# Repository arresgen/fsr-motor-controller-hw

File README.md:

# Op-Amp & Comparator Controller Board

A KiCad hardware design project featuring an operational amplifier signal conditioning circuit and comparator-driven DC motor and LED indicator control.

---

## Technical Specifications & Features

* **Primary Supply Voltage:** +5V DC
* **Operational Amplifier:** Texas Instruments LM358 (Dual Low-Power Op-Amp)
* **Comparator:** Texas Instruments LM393 (Dual Low-Power Comparator)
* **Sensor Connector:** JST-EH 2-Pin header labeled for Force Sensitive Resistor (FSR402)
* **Actuator Output:** Transistor-driven (2N2222 NPN) DC Motor driver stage with flyback diode protection (1N4007)
* **Visual Indicator:** LED status circuit (D1) driven via comparator thresholding
* **Test Points:** Dedicated test points (`TP1` through `TP6`) for signal probing and hardware validation
* **Form Factor:** Compact 2-layer PCB (50.8 mm x 76.2 mm / KiCad 10.0 standard layer stack)[cite: 2]

---

## Circuit Overview

1. **Input Stage:** The input signal connects via connector `J1` (FSR402 sensor). Resistors `R1` (1.5k) and `R2` (10k) provide biasing and initial signal division.
2. **Amplification & Conditioning Stage (LM358):** Unit `U1` buffers and amplifies the analog input signal. Potentiometer `RV1` (10k) allows adjustable gain/reference tuning.
3. **Thresholding & Comparison Stage (LM393):** Dual comparator `U2` compares the processed signal against adjustable resistor network references (`R3` 100k, `R4` 6.8k).
4. **Output Driver Stage:**
   * **LED Drive:** Open-collector output drives status LED `D1` through limiting resistor `R6` (4.7k).
   * **Motor Drive:** Comparator output switches NPN transistor `Q2` (2N2222) via base resistor `R7` (100Ω) to power DC Motor `M1`. Free-wheeling diode `D2` (1N4007) suppresses inductive voltage spikes.

---

## Component List (BOM)

| Reference | Value / Part | Description | Footprint / Package |
| :--- | :--- | :--- | :--- |
| **U1** | LM358 | Low-Power Dual Op-Amp | DIP-8 Socket |
| **U2** | LM393 | Dual Voltage Comparator | DIP-8 Socket |
| **Q2** | 2N2222 | General Purpose NPN Transistor | TO-92L Inline Wide |
| **D1** | LED | Status Indicator | JST-EH 2-Pin / THT |
| **D2** | 1N4007 | 1000V 1A Rectifier Diode | DO-41 Horizontal |
| **M1** | Motor_DC | DC Motor Output | JST-EH 2-Pin Header |
| **J1** | FSR402 | Sensor Connector Input | JST-EH 2-Pin Vertical |
| **J2** | DC Source | +5V / GND Power Input | JST-EH 2-Pin Vertical |
| **RV1** | 10k | Potentiometer | JST-EH 3-Pin / Trim Pot |
| **R1** | 1.5k | Axial Resistor, 1/4W | DIN0207 (10.16mm Pitch) |
| **R2, R5** | 10k, 1k | Axial Resistors, 1/4W | DIN0207 (10.16mm Pitch) |
| **R3, R4** | 100k, 6.8k | Axial Resistors, 1/4W | DIN0207 (10.16mm Pitch) |
| **R6, R7** | 4.7k, 100 | Axial Resistors, 1/4W | DIN0207 (10.16mm Pitch) |
| **C1 - C5** | 100n / 22n | Ceramic Disc Decoupling Capacitors | Disc D5.0mm / P5.00mm |

---

## Test Point Reference

* **TP1:** Input signal node post-FSR biasing stage
* **TP2:** Non-inverting operational amplifier stage output/input node
* **TP3:** Voltage reference/bias node
* **TP4:** Comparator output signal node
* **TP5:** Secondary op-amp output stage
* **TP6:** Motor drive / low-side control node

---

## Project Structure

```text
.
├── fsr-motor-controller-hw.kicad_sch    # Schematic Source File
├── fsr-motor-controller-hw.kicad_pcb    # PCB Layout Source File
└── README.md                                  # Documentation

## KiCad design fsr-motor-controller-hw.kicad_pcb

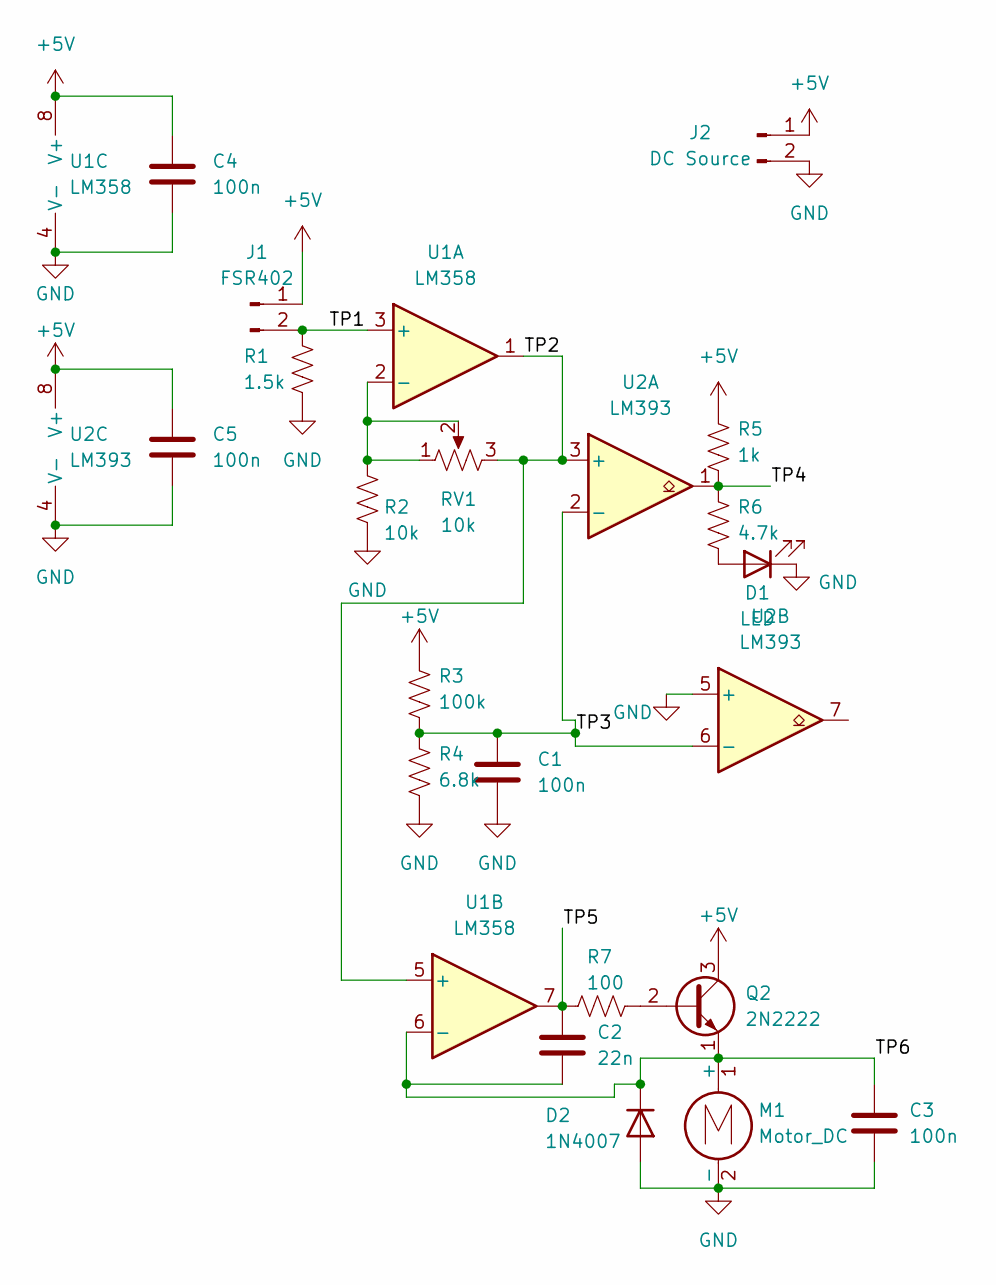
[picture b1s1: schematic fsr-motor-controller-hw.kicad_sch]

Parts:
C1, C3, C4, C5: 100n; C_Disc_D5.0mm_W2.5mm_P5.00mm
C2: 22n; C_Disc_D5.0mm_W2.5mm_P5.00mm
D1: LED; JST_EH_B2B-EH-A_1x02_P2.50mm_Vertical
D2: 1N4007; D_DO-41_SOD81_P10.16mm_Horizontal
J1: FSR402; JST_EH_B2B-EH-A_1x02_P2.50mm_Vertical
J2: DC Source; JST_EH_B2B-EH-A_1x02_P2.50mm_Vertical
M1: Motor_DC; JST_EH_B2B-EH-A_1x02_P2.50mm_Vertical
Q2: 2N2222; TO-92L_Inline_Wide
R1: 1.5k; R_Axial_DIN0207_L6.3mm_D2.5mm_P10.16mm_Horizontal
R2: 10k; R_Axial_DIN0207_L6.3mm_D2.5mm_P10.16mm_Horizontal
R3: 100k; R_Axial_DIN0207_L6.3mm_D2.5mm_P10.16mm_Horizontal
R4: 6.8k; R_Axial_DIN0207_L6.3mm_D2.5mm_P10.16mm_Horizontal
R5: 1k; R_Axial_DIN0207_L6.3mm_D2.5mm_P10.16mm_Horizontal
R6: 4.7k; R_Axial_DIN0207_L6.3mm_D2.5mm_P10.16mm_Horizontal
R7: 100; R_Axial_DIN0207_L6.3mm_D2.5mm_P10.16mm_Horizontal
RV1: 10k; JST_EH_B3B-EH-A_1x03_P2.50mm_Vertical
U1: LM358; DIP-8_W7.62mm_Socket_LongPads
U2: LM393; DIP-8_W7.62mm_Socket_LongPads

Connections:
+5V: C4.1, C5.1, J1.1, J2.1, Q2.3 (C), R3.1, R5.1, U1.8 (V+), U2.8 (V+)
/TP1: J1.2, R1.1, U1.3 (+)
/TP2: RV1.3, U1.1, U1.5 (+), U2.3 (+)
/TP3: C1.1, R3.2, R4.1, U2.2 (-), U2.6 (-)
/TP4: R5.2, R6.1, U2.1
/TP5: C2.1, R7.1, U1.7
/TP6: C2.2, C3.1, D2.1 (K), M1.1 (+), Q2.1 (E), U1.6 (-)
GND: C1.2, C3.2, C4.2, C5.2, D1.1 (K), D2.2 (A), J2.2, M1.2 (-), R1.2, R2.2, R4.2, U1.4 (V-), U2.4 (V-), U2.5 (+)
unnamed: D1.2 (A), R6.2
unnamed: Q2.2 (B), R7.2
unnamed: R2.1, RV1.1, RV1.2, U1.2 (-)

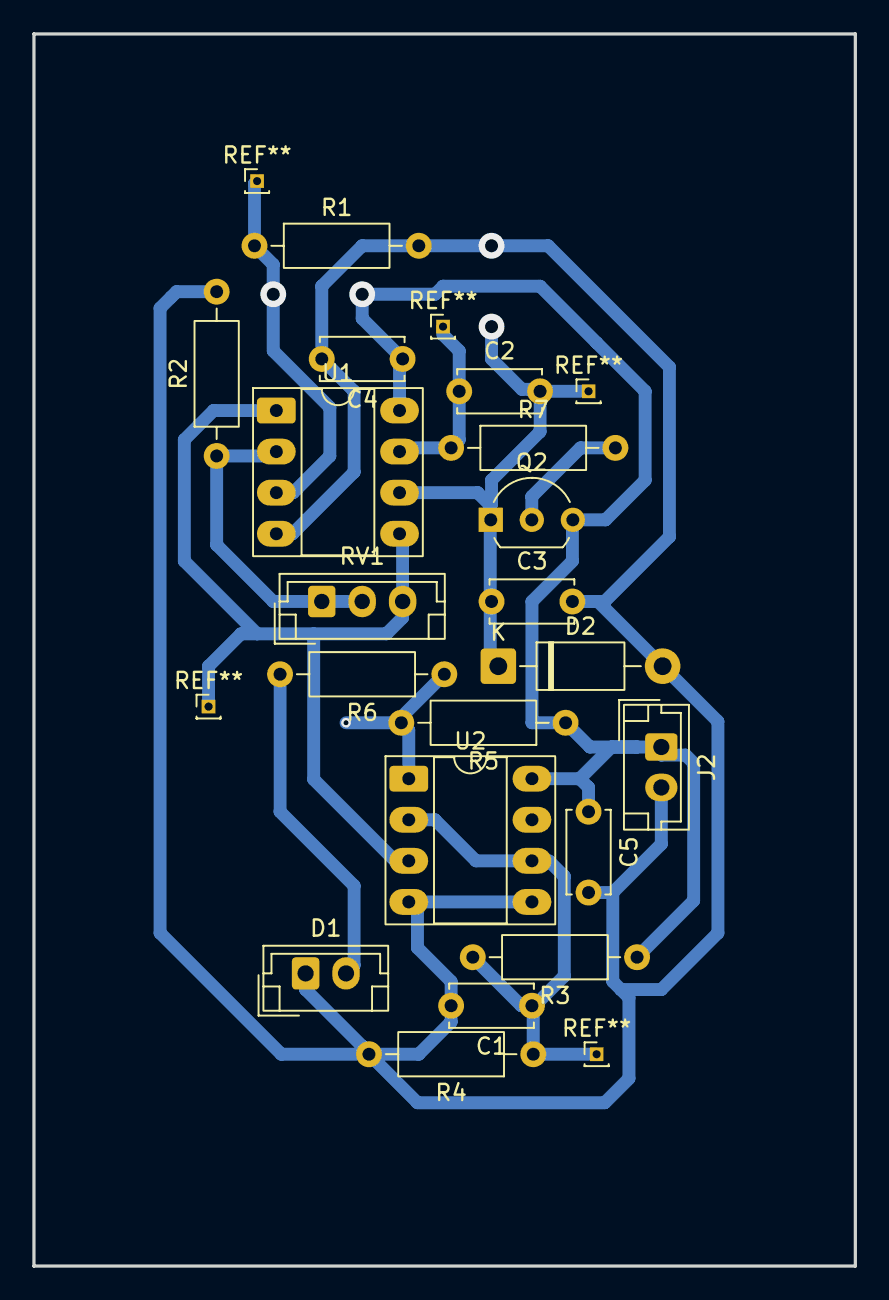
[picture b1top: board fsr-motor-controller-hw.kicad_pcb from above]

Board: 2 copper layers, 50.8 x 76.2 mm, 19 parts (0 on the bottom side), 11 nets.
